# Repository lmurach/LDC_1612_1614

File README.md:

# Inductance to Digital Converter Library for the LDC1312, LDC1314, LDC1612, and LDC1614

<hr>

## Introduction

This library serves as an alternative to the library created by SEEED that incorporates the ability to use the 4 channel chip and instructions on how to set up a working version without using the Grove demo board. This sheet will explain everything you need to maximize accuracy for your own LDC, how to calculate every parameter required for calculations, a sample PCB design, and how to set up an Arduino program.

## Usage

(will fill in with installation instructions when the library is able to be installed through Arduino)

In order to use the installed library, put the following code up top. Change the LDC1612 value to the name of your LDC chip (LDC1312, LDC1314, LDC1612, and LDC1614 are the 4 accepted types):
```c
#include "LDC_1612_1614.h"
LDC_1612_1614 ldc(LDC1612);
```
Then write ldc. before each function. Function names and purposes can be found at the [bottom of this page](https://github.com/Quillington/LDC_1612_1614/blob/master/README.md#code-functions). See examples for more clarity.

## Setup

### Hardware

#### Grove Board
Choose which channel you want to use (0 or 1 for LDC1612, 0, 1, 2, or 3 for LDC1614). Connect each end to the Ch0 pins or Ch1 pins. Remember which channel you use, its important for the code setup. Plug the Grove connector into the board. Match up the ground, Vcc, SDA, and SCL pins on the Arduino.

#### Only the Chip
Connect a coil and a small capacitor (such as 100 pf) in parallel. Choose which channel you want to use (0 or 1 for LDC1612, 0, 1, 2, or 3 for LDC1614). Connect one end to the INA pin for your channel and the other end to the INB pin. Remember which channel you use, its important for the code setup. A 40MHz crystal oscillator is optimal for the CLKIN, otherwise the internal clock can be used. The library has a function to swap to the internal clock. Connect up the pins to match the pins on the Arduino. The ADDR pin should high. If it is low, then you will need to use the function to change the I2C address. These pins are the same on the LDC13 series.

### Finding Your Coil's Parameters

In order to have accurate calculations, there are 3 required parameters in the configure_channel() function. These parameters are 
1. **Inductance** - This is the amount of inductance in micro Henries (µH) of the coil. Do NOT count parasitic resistance, only the coil's inductance. There are many online calculators that can be used to get an estimate such as [this one](http://www.circuits.dk/calculator_flat_spiral_coil_inductor.htm) for flat coils or [this one](https://www.allaboutcircuits.com/tools/coil-inductance-calculator/) for cylindrical air coils. The default value for the 20 turn Groce inductive coil is 18.147. To get a better estimate, see the section below.
2. **Capacitance** - This is the amount of capacitance put in parallel with the coil inductor in pico Ferads (pF). The default value for the Grove inductive sensor is 100.
3. **Rp** - This is a representation of parasitic resistance and inductance. The details on the specifics can be found [here](https://www.ti.com/lit/an/snaa221b/snaa221b.pdf?ts=1687778558050&ref_url=https%253A%252F%252Fwww.ti.com%252Fproduct%252Fde-de%252FLDC1612). The default value for the grove 20 turn coil is 15.727. Measuring this value for homemade coils can be achieved in several different methods outlined by TI in [this document](https://www.ti.com/lit/an/snoa936/snoa936.pdf?ts=1687797220953&ref_url=https%253A%252F%252Fwww.google.com%252F). The method that only involves an oscilloscope and function generator is outlined below with pictures.

### Measuring Rp and Inductance

Make sure that you have a function generator, variable resistor/potentiometer (one that goes up to 100k is ideal), and 2-channel oscilloscope before you begin. The faster the ocilloscope and function generator, the better. The goal is to find the resonant frequency which is about 3.75MHz for the sample Grove coil. Both the function generator and the ocilloscope needs to be able to handle that frequency, ideally higher. If you do not have a good setup, a higher capacitor instead of the typical 100pF.
1. Setup this circuit

<ol start=2>
  <li>Hold metal near your coil at the maximum distance you desire to measure metal.</li>
  <li>Change the frequency of the scope until the input and output channel match phase. The output's amplitude should peak at this point. This is the resonant frequency. Pictured below: Not in resonance (left) and in resonance (right).</li>

<ol start=4 type="1">
  <li>At this point the inductance can be calculated with resonant frequency. Use the equation L = (C/(2πf)^2) or <a href="https://www.omnicalculator.com/physics/resonant-frequency-lc">this calculator</a>. With the values of C=100pf and f= 3.68MHz, the calculated value for L is 18.7, which is very close to the expected L of 18.1.</li>
  <li>Now, adjust the resistor so that the output is 4x smaller than the input. 2x can also be used for less current consumption, but 4x is the recommeneded amount. Below 2x was used, notice the scale on the scope.</li>
</ol>

### Making sure the Parameters are in the Measurable Range

The chip has limitations on what it can measure. The frequency and Rp must be within a certain range.
<ol type="1">
  <li> **Frequency must be above 1kHz** - If it is not, then then the capacitance should be decreased.</li>
  <li> **Frequency must be under 10MHz** - If it is not, then the capacitance should be increased.</li>
  <li> **Rp must be under 90k** - If it is not, then a small (100 ohm or so) resistor must be added in parallel.</li>
</ol>

Note that changing either of these two values requires redoing both of the measurements.

## Code Functions
```
configure_channel(uint8_t channel, float inductance, float capacitance, float Rp);
```
This function must be used in the initial setup before any information can be pulled out of the chip. Use the values found earlier. It returns void. (No value)
```
get_channel_data(uint8_t channel);
```
This function returns a 32 bit unsigned value that changes based on inductance. The change in this value represents an increase or decrease in inductance. See the demo Arduino files for possible applications.
```
change_I2C_address();
```
The I2C address is 0x2B by default. If the LDC ADDR pin is held low, it becomes 0x2A. Do NOT use this function if using a Grove board, as the ADDR pin is always held high.
```change_I2C_address(0)```
changes the address to 0x2A
```change_I2C_address(1)```
changes the address to 0x2B (default)
```
change_clock_mode(bool mode);
```
This function allows the use of the internal clock. Note: this should only be used if an external clock is not present or permitted in the design. Use the following values:
```change_clock_mode(INTERNAL)``` 
changes to the internal clock.
```change_clock_mode(EXTERNAL)``` 
changes to the external clock. (default)

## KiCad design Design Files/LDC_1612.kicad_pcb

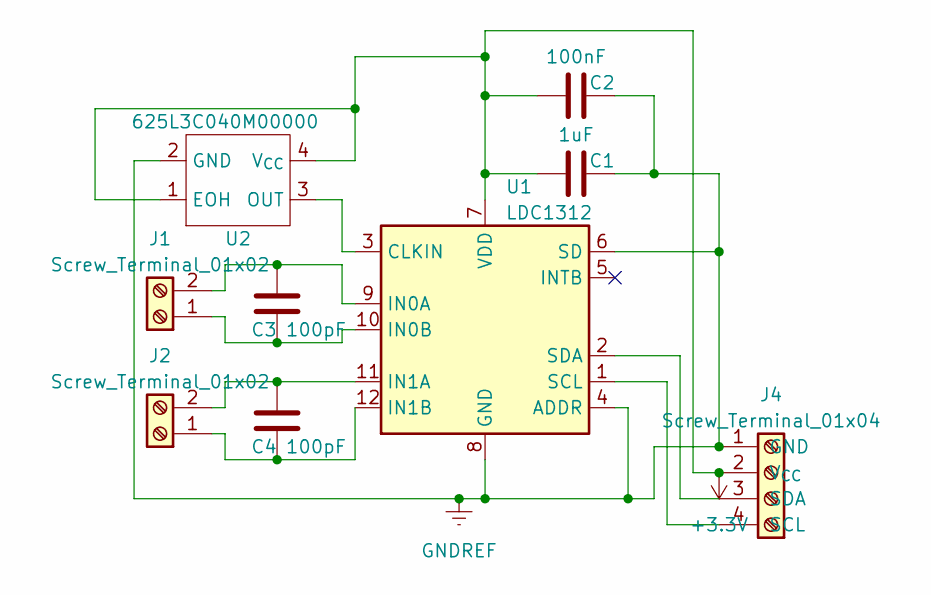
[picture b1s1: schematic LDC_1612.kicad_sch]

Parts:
C1: 1uF; C_0805_2012Metric_Pad1.18x1.45mm_HandSolder
C2: 100nF; C_0805_2012Metric_Pad1.18x1.45mm_HandSolder
C3, C4: 100pF; C_0805_2012Metric_Pad1.18x1.45mm_HandSolder
J1, J2: Screw_Terminal_01x02; 2_pin_connector
J4: Screw_Terminal_01x04; NS-Tech_Grove_1x04_P2mm_Vertical
U1: LDC1312; WSON-12-1EP_4x4mm_P0.5mm_EP2.6x3mm_ThermalVias
U2: 625L3C040M00000

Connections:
+3.3V: C1.2, C2.2, J4.2 (V_{CC}), U1.7 (VDD), U2.1 (EOH), U2.4 (V_{CC})
GNDREF: C1.1, C2.1, J4.1 (GND), U1.4 (ADDR), U1.6 (SD), U1.8 (GND), U1.13 (GND), U2.2 (GND)
unnamed: C3.2, J1.1, U1.10 (IN0B)
unnamed: C3.1, J1.2, U1.9 (IN0A)
unnamed: C4.2, J2.1, U1.12 (IN1B)
unnamed: C4.1, J2.2, U1.11 (IN1A)
unnamed: J4.4 (SCL), U1.1 (SCL)
unnamed: J4.3 (SDA), U1.2 (SDA)
unnamed: U1.3 (CLKIN), U2.3 (OUT)

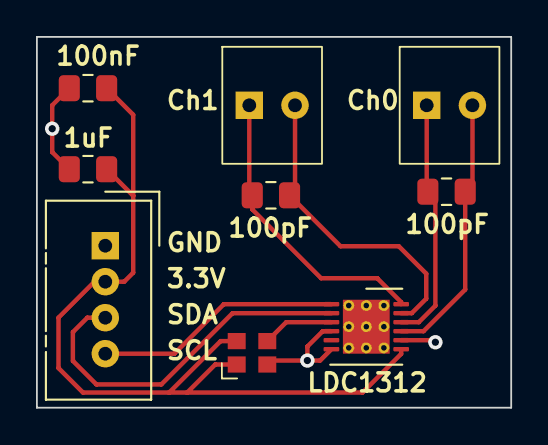
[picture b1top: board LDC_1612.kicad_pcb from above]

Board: 2 copper layers, 26.3 x 20.6 mm, 9 parts (0 on the bottom side), 9 nets.

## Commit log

2023-06-22 Add .gitattributes, .gitignore, README.md, and LICENSE.txt.
2023-06-22 Arduino code carried over
2023-06-22 bug fixes
2023-06-22 Progress on debugging the I2C
2023-06-23 All config registers now read back correct values
2023-06-23 get_channel_result now prints correctly
2023-06-26 Fixed channel 1 config
2023-06-26 Fixed Support for LDC1614
2023-06-26 Errors now print with helpful messages
2023-06-27 New Errors added and tested
2023-06-27 Changed max frequency from 33MHz to 10MHz
2023-06-27 Changed max frequency to 33MHz to 10MHz
2023-06-27 Added a minimum frequency
2023-06-28 Fixed frequency values and Rp Section
2023-06-30 Rp Update
2023-06-30 link update
2023-06-30 refinement and added more functions
2023-07-05 Minor Error Changes
2023-07-05 added new functions (not tested)
2023-07-06 Fixed pointer comparison in mux config
2023-07-11 Fixed Rp Instructions
2023-07-23 Fixed Compile Errors
2023-07-23 removed debug prints and return error
2023-10-23 Added design files
